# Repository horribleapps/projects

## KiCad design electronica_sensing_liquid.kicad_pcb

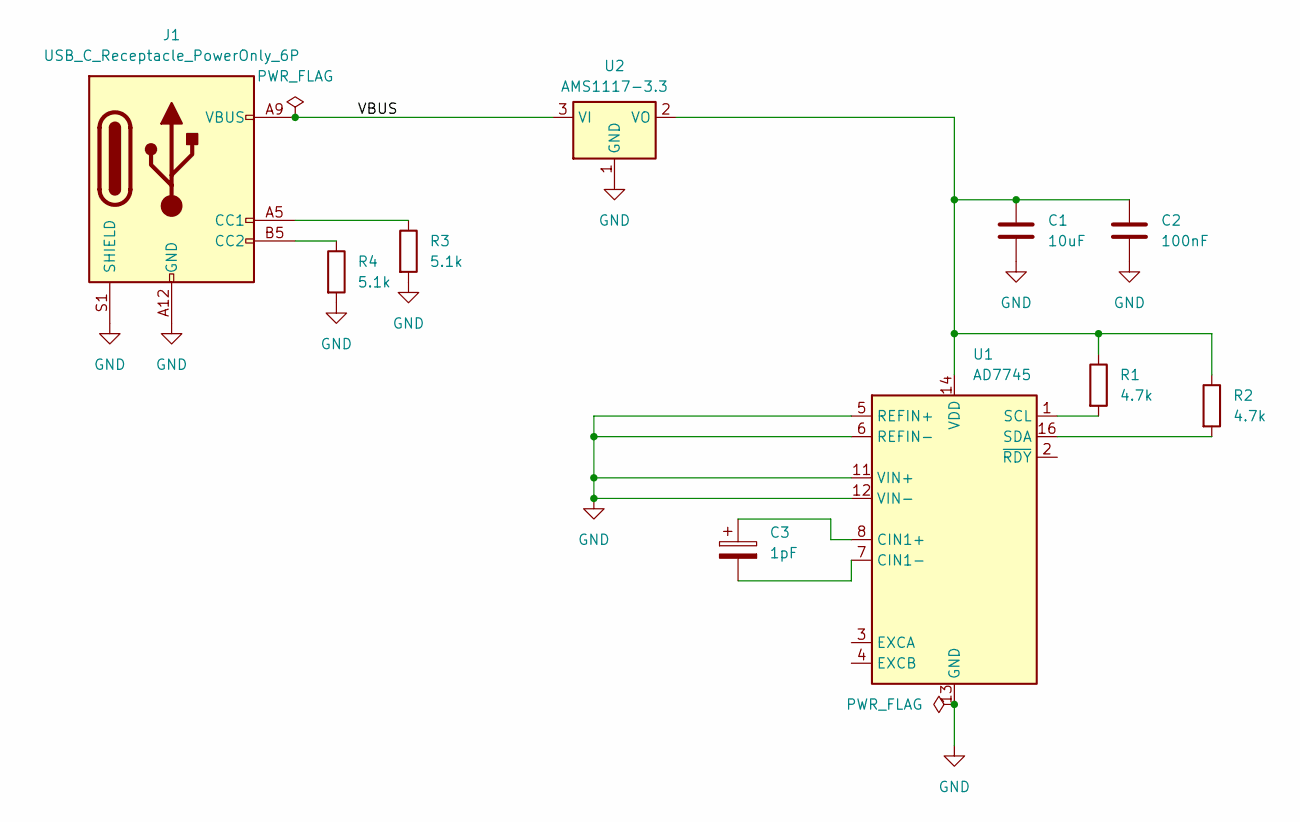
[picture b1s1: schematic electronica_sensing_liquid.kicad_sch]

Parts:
C1: 10uF; C_0603_1608Metric
C2: 100nF; C_0603_1608Metric
C3: 1pF; C_1206_3216Metric
J1: USB_C_Receptacle_PowerOnly_6P; USB_C_Receptacle_GCT_USB4125-xx-x-0190_6P_TopMnt_Horizontal
R1, R2: 4.7k; R_0603_1608Metric
R3, R4: 5.1k; R_0603_1608Metric
U1: AD7745; TSSOP-16_4.4x5mm_P0.65mm
U2: AMS1117-3.3; SOT-223-3_TabPin2

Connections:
/VBUS: J1.A9 (VBUS), J1.B9 (VBUS), U2.3 (VI)
GND: C1.2, C2.2, J1.A12 (GND), J1.B12 (GND), J1.S1 (SHIELD), R3.2, R4.2, U1.5 (REFIN+), U1.6 (REFIN-), U1.11 (VIN+), U1.12 (VIN-), U1.13 (GND), U2.1 (GND)
unnamed: J1.A5 (CC1), R3.1
unnamed: J1.B5 (CC2), R4.1
unnamed: C3.1, U1.8 (CIN1+)
unnamed: C3.2, U1.7 (CIN1-)
unnamed: R1.2, U1.1 (SCL)
unnamed: R2.2, U1.16 (SDA)
unnamed: C1.1, C2.1, R1.1, R2.1, U1.14 (VDD), U2.2 (VO)

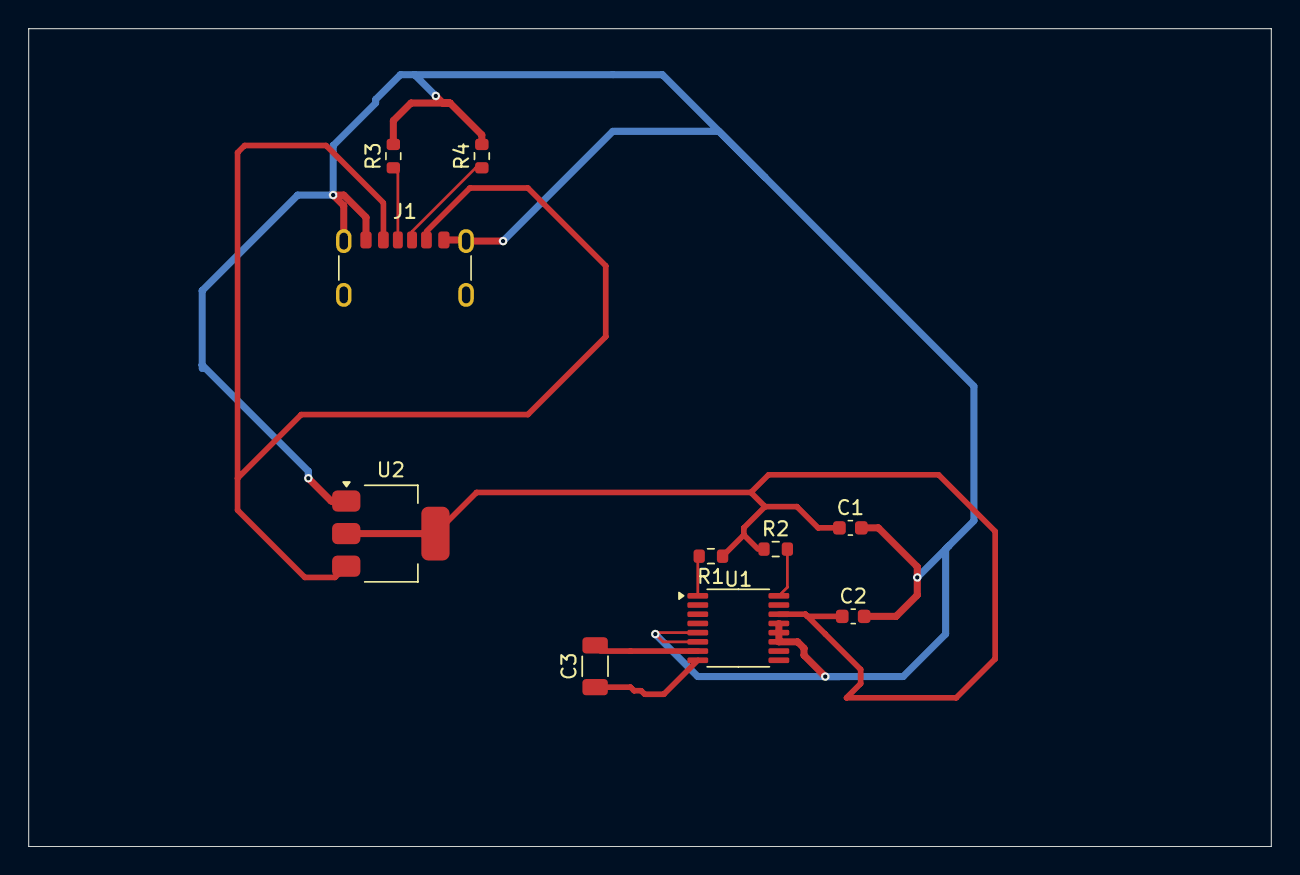
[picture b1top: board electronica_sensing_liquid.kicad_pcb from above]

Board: 2 copper layers, 87.8 x 57.8 mm, 10 parts (0 on the bottom side), 9 nets.

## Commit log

2024-06-24 added way to stream images and added ways to detect templates, plus sign is the best
2024-06-30 added code for reading cam from usb and doing template matching, and recognizing speech and converting to text
2024-08-05 added code for scraping images
2024-12-28 added electronic sensing files
2024-12-28 freecad files
    freecad files
